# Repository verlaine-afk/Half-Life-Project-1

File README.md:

My Half week 1 PCB Project
What is this?
This is my PCB project for Hack Club’s Half Life. I’m making an ESP32-based project and designing a custom PCB for it.

I wanted to use this project to get more comfortable with PCB design, electronics, and coding.

What I’ve Done
So far, I’ve:

Designed the PCB in KiCad
Made a custom bat-shaped board outline
Learned how Edge.Cuts works
Started setting up the ESP32
Set up ESP32 boards in Arduino IDE
Started working on the code
Tested and verified parts of the code without the physical board
My Process
I started by making the basic shape of the PCB and adjusting it until I was happy with it. I decided to make it a bat shape instead of just using a basic rectangle.

After that, I started working on the electronics and ESP32 setup. I’ve also been learning how the Arduino code connects to what I want the actual project to do.

Since I don’t have the physical PCB yet, I’ve mainly been working on the design and code that I can test without the hardware.

What I Learned
I’ve learned a lot about KiCad and PCB design while working on this. I also got more familiar with ESP32 boards and how to set them up in Arduino IDE.

One thing I’ve learned is that things don’t always work the first time, so I’ve had to change things and figure out what was causing problems along the way.

Current Progress
The PCB design is still being worked on, and I’m continuing to work on the Arduino code, I got really busy with making different images so my "pet" changes depending on what it does to make the project a bit more fun and interactive.

My next step is to finish up the design and eventually test everything with the actual hardware.

What I Want to Add Later
Finish the PCB
Test it with the actual ESP32
Test the code on the hardware
Fix anything that doesn’t work
Add more features if I have time

Schematic Sketch:

PCB design:

3D View:

Examples of codes I added myself:

Art I made:

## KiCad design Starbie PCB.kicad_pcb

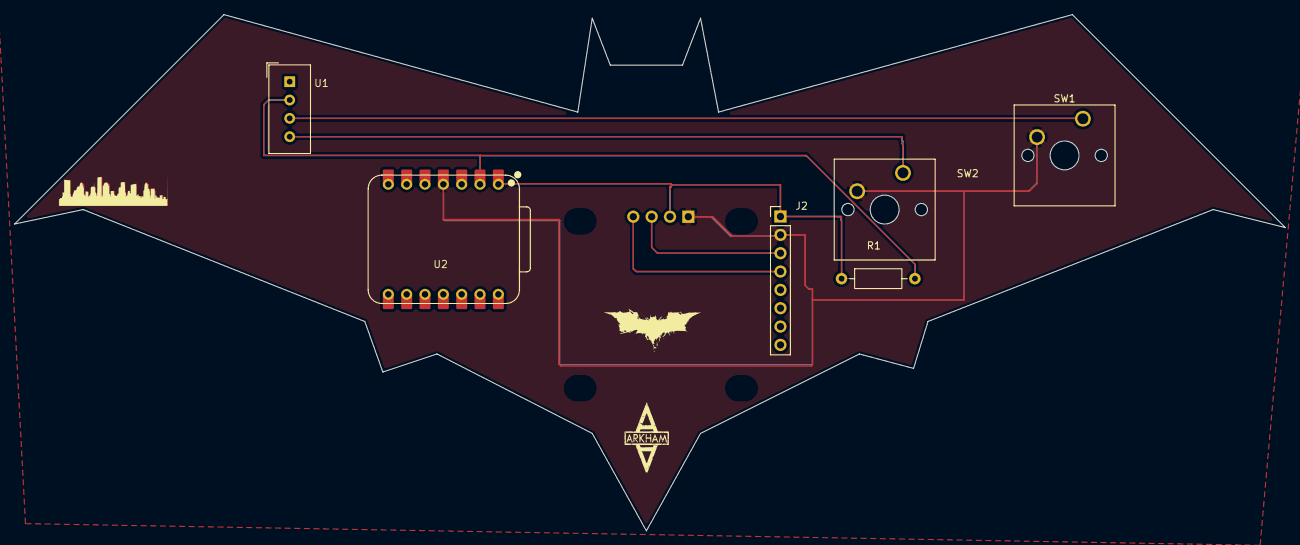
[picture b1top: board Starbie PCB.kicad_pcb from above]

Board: 2 copper layers, 176.0 x 71.5 mm, 7 parts (1 on the bottom side), 7 nets.

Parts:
J1: Conn_01x04_Pin; Display_128x64_096_I2C
J2: Conn_01x08_Pin; PinHeader_1x08_P2.54mm_Vertical
R1: 10k; R_Axial_DIN0207_L6.3mm_D2.5mm_P10.16mm_Horizontal
SW1, SW2: SW_Push; SW_Cherry_MX_1.00u_PCB
U1: XIAO-ESP32-C3-SMD; Aosong_DHT11_5.5x12.0_P2.54mm
U2: DHT11; XIAO-ESP32-C6-DIP

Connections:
+3.3V: J1.2, J2.1, R1.1, U2.1 (VDD)
/DHT11 DATA: R1.2, U1.2 (D1), U2.2 (DATA)
/GPIO2: SW1.1, U1.3 (D2)
/GPIO3: SW2.1, U1.4 (D3)
/SCL: J1.3, J2.3
/SDA: J1.4, J2.4
GND: J1.1, J2.2, SW1.2, SW2.2, U2.4 (GND)
